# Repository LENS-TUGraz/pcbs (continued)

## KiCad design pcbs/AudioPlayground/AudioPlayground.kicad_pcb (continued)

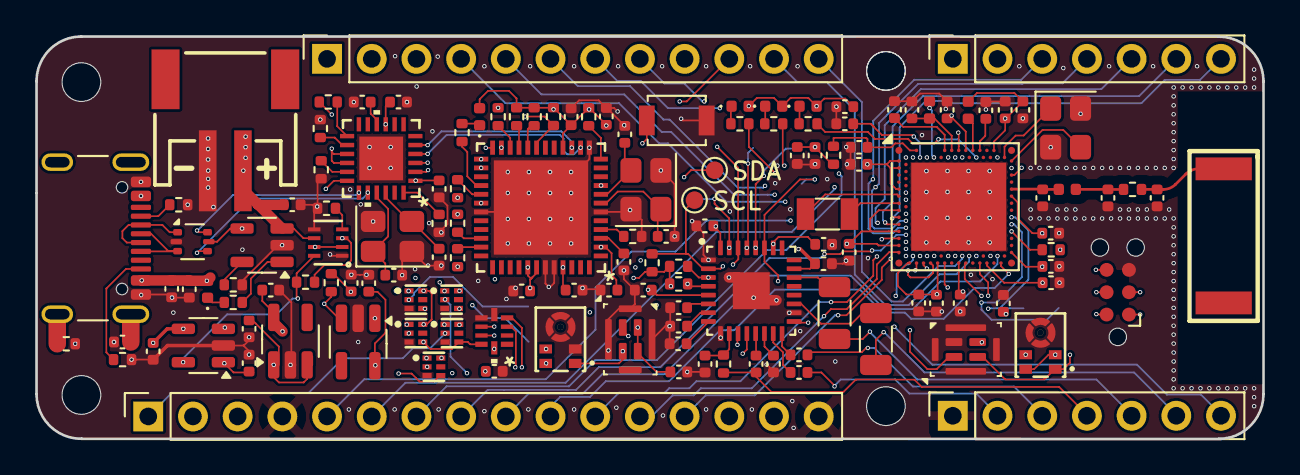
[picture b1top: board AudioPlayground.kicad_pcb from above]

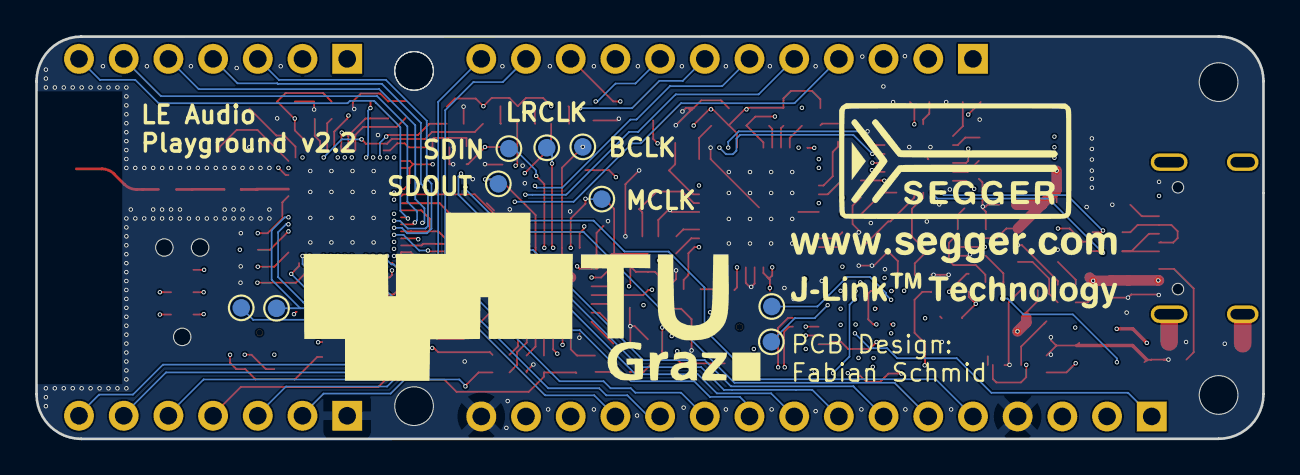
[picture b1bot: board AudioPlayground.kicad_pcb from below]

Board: 6 copper layers, 69.7 x 22.9 mm, 146 parts (9 on the bottom side), 129 nets.

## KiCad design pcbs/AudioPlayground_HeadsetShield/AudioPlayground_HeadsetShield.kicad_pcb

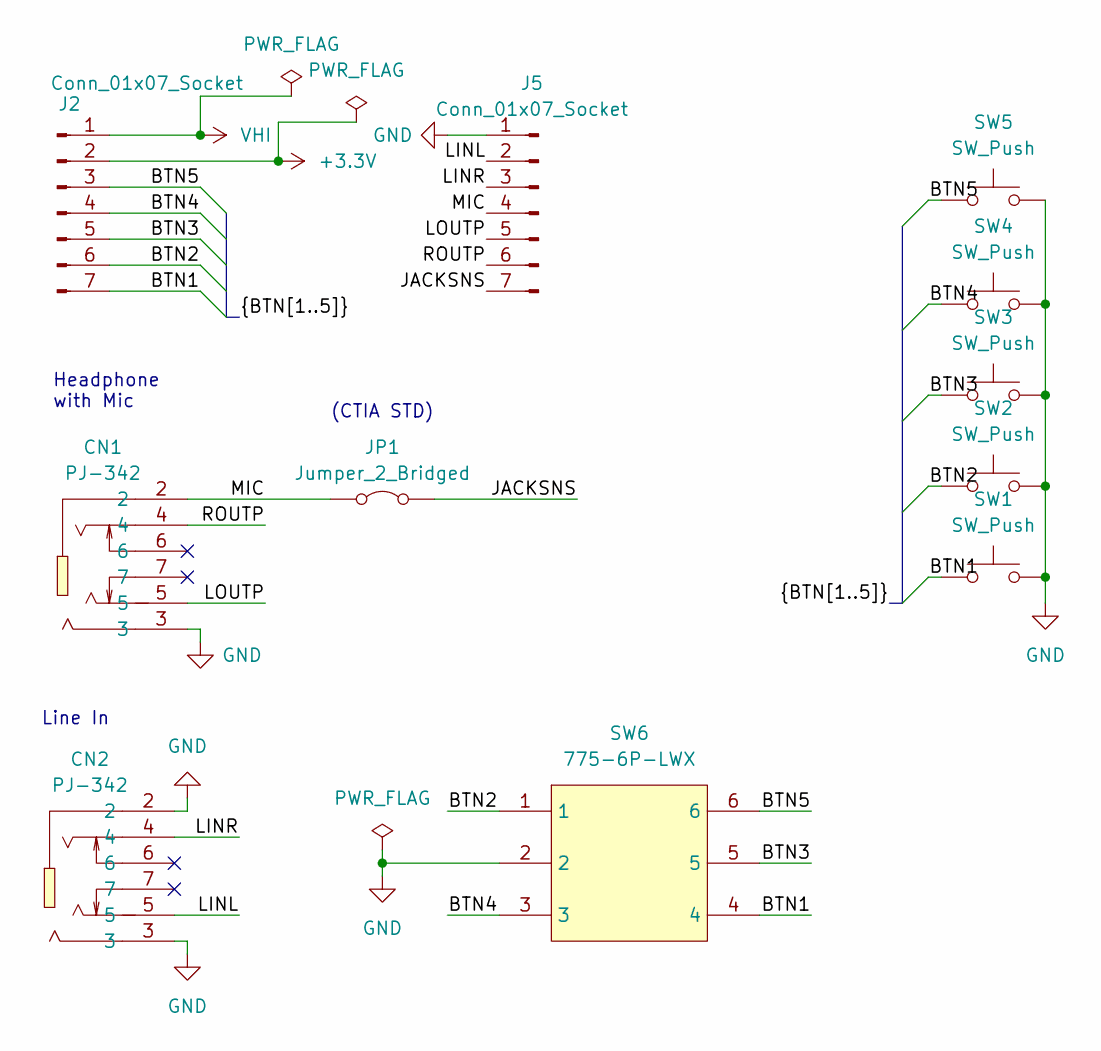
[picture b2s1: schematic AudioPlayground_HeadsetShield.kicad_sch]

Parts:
CN1, CN2: PJ-342; LCSC Part C668606
J2, J5: Conn_01x07_Socket; PinHeader_1x07_P2.54mm_Vertical_SMD_Pin1Left; LCSC C2883764
JP1: Jumper_2_Bridged; SolderJumper-2_P1.3mm_Bridged2Bar_RoundedPad1.0x1.5mm
SW1, SW2, SW3, SW4, SW5: SW_Push; SW_SPST_B3U-1000P; MOUSER 653-B3U-1000P
SW6: 775-6P-LWX; LCSC Part C2858287

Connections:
+3.3V: J2.2
/BTN1: J2.7, SW1.1, SW6.4
/BTN2: J2.6, SW2.1, SW6.1
/BTN3: J2.5, SW3.1, SW6.5
/BTN4: J2.4, SW4.1, SW6.3
/BTN5: J2.3, SW5.1, SW6.6
/JACKSNS: J5.7, JP1.2 (B)
/LINL: CN2.5, J5.2
/LINR: CN2.4, J5.3
/LOUTP: CN1.5, J5.5
/MIC: CN1.2, J5.4, JP1.1 (A)
/ROUTP: CN1.4, J5.6
GND: CN1.3, CN2.2, CN2.3, J5.1, SW1.2, SW2.2, SW3.2, SW4.2, SW5.2, SW6.2
VHI: J2.1

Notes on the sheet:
Line In
(CTIA STD)
Headphone with Mic

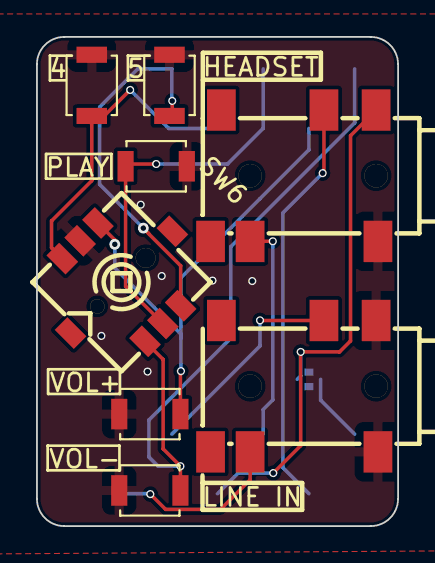
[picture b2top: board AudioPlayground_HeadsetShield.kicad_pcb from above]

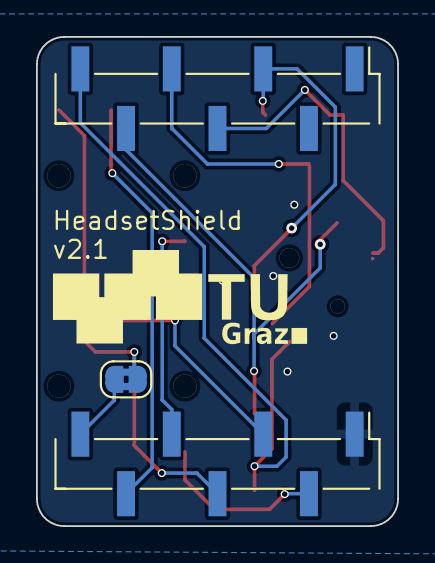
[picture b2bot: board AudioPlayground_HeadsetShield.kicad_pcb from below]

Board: 2 copper layers, 20.1 x 27.2 mm, 11 parts (3 on the bottom side), 12 nets.

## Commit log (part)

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2025-10-22 Add .gitignore
2025-10-22 Add Components
2025-10-22 Add PCB Structure
2025-10-25 added AudioPlayground and AudioPlayground_HeadsetShield
2025-10-26 updated footprints, added i2s testpoints
2025-11-06 added usb221, removed usb connections from bus-switch.
2025-11-06 changed battery connector back to original, moved reset button so it is accessible when audio shield is on
2025-11-14 Add LCSC and fix RF
2025-11-14 Fix values
2025-11-14 Fix 3d
2025-11-14 Fix Silkscreen
2025-11-17 Update MICs
2025-11-17 Fix unconnected traces
2025-11-18 Add HeadsetShield v2.0
2025-11-18 Fix Codec IRQ
2025-11-18 Fix Naming
2025-11-18 Fix USB Pullups
2025-11-19 Fix Antenna Trace
2025-11-21 Add Test Points
2025-12-22 Change Analog Switches
2025-12-22 Update Analog Switches
2025-12-22 moved interface MCU LED to 3.3V switched
2025-12-23 Cleanup
2025-12-23 V2.1
2026-01-21 Add Mounting Holes
2026-01-21 Fix IC Markings
2026-01-21 Fix Headset Shield
2026-01-21 Fix Silk
2026-01-21 Fix Joystick
2026-01-22 Fix LED Brightness
2026-01-29 Add Gerbers
2026-02-05 Fix Renderings
2026-02-16 Improve Optic
